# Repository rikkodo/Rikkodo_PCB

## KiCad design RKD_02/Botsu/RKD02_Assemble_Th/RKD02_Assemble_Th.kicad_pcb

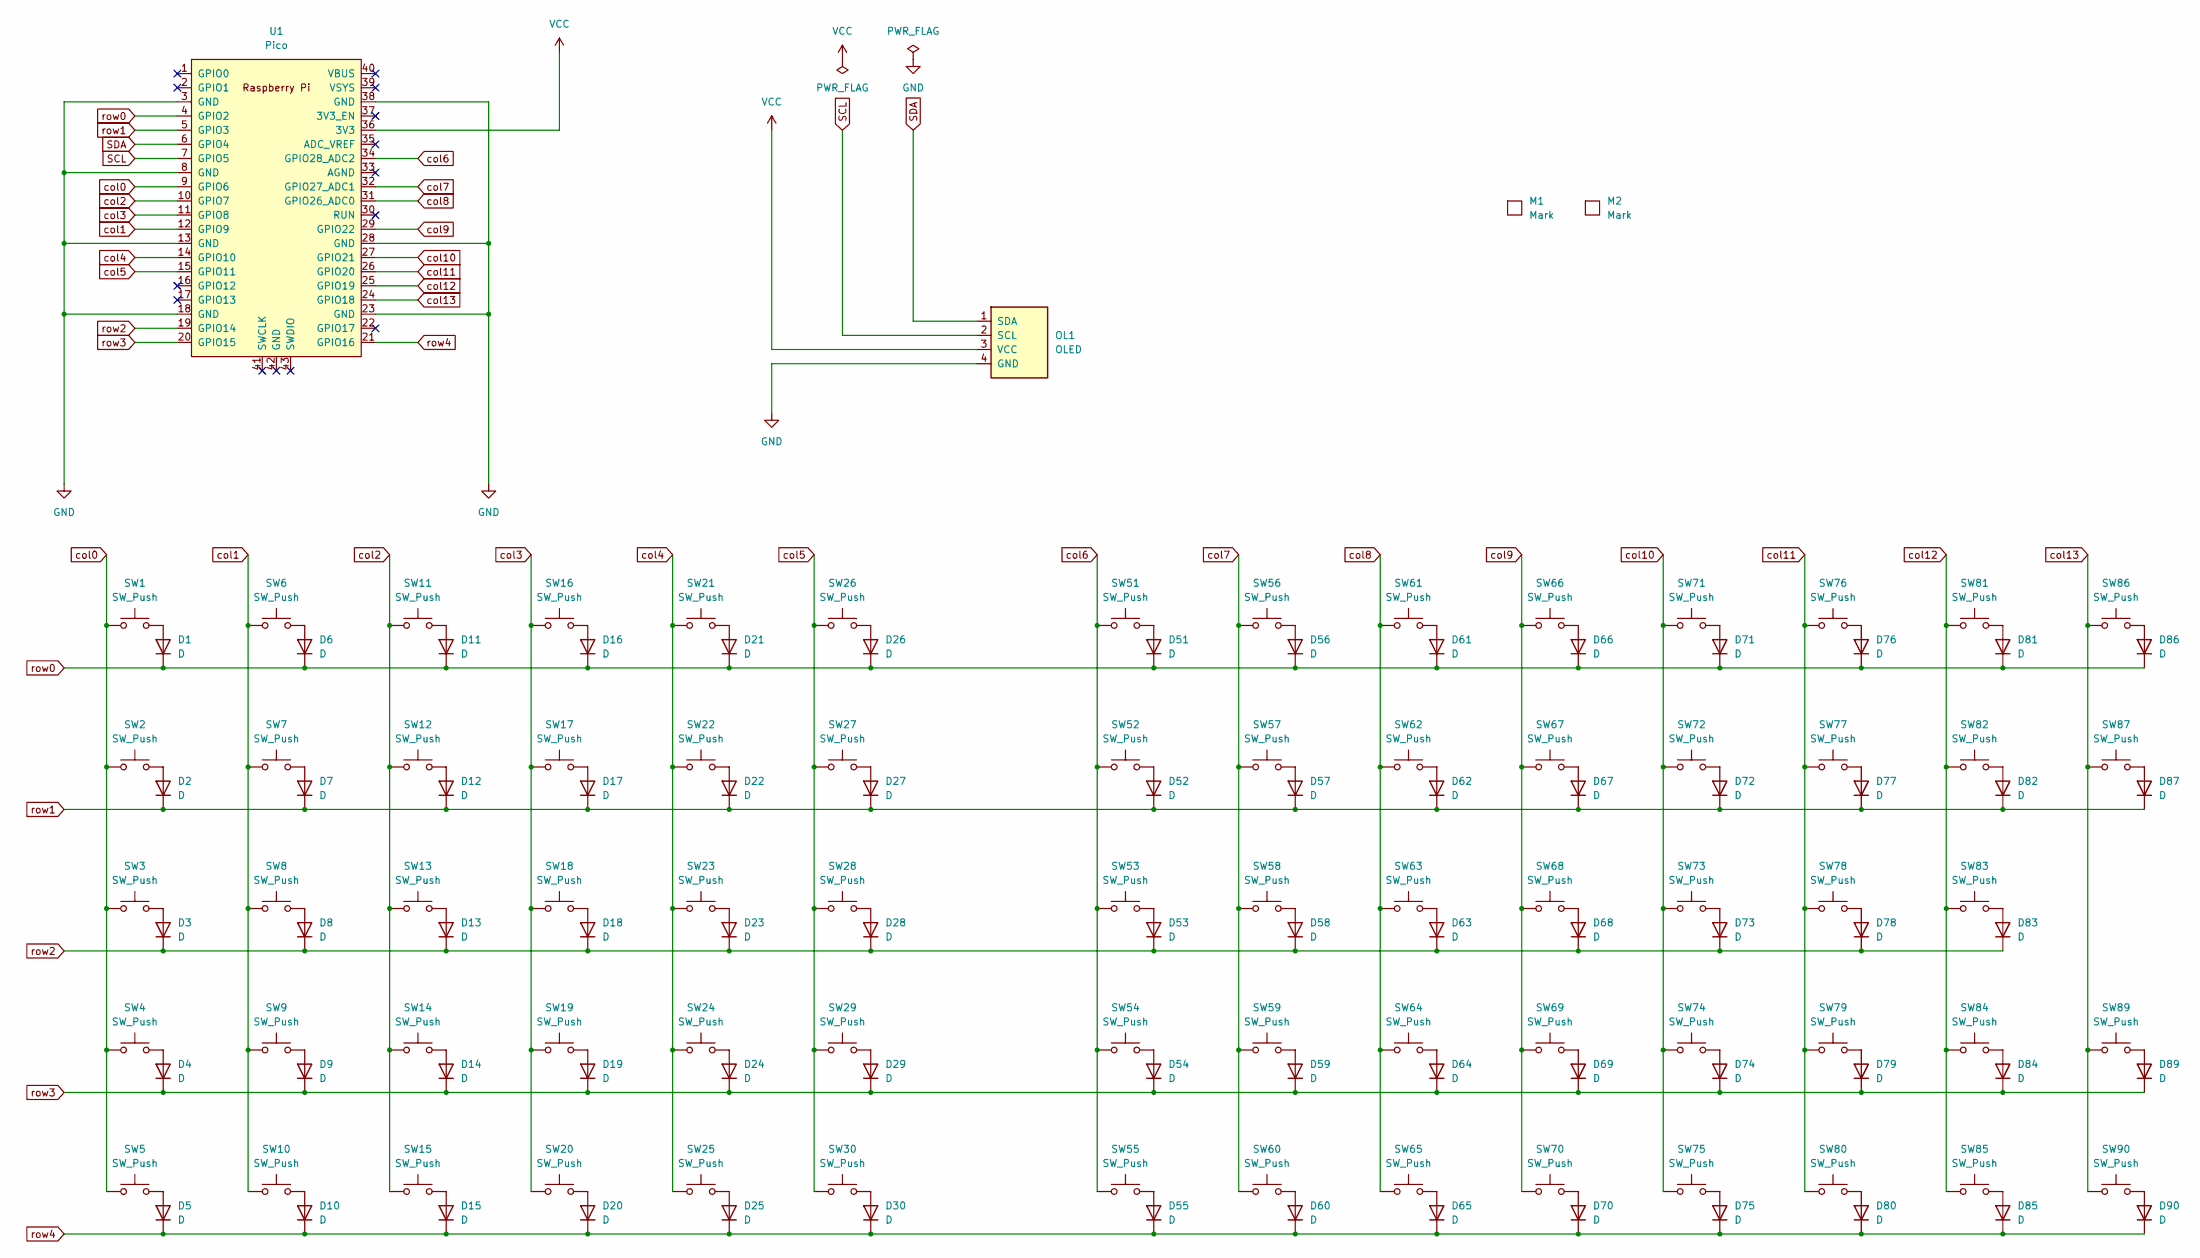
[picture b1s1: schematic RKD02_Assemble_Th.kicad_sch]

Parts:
D1, D2, D3, D4, D5, D6, D7, D8, D9, D10, D11, D12, D13, D14, D15, D16, D17, D18, D19, D20, D21, D22, D23, D24, D25, D26, D27, D28, D29, D30, D51, D52, D53, D54, D55, D56, D57, D58, D59, D60, D61, D62, D63, D64, D65, D66, D67, D68, D69, D70, D71, D72, D73, D74, D75, D76, D77, D78, D79, D80, D81, D82, D83, D84, D85, D86, D87, D89, D90: D; Diode_SMD
M1: Mark; rkd_Guard_Screw_Hall
M2: Mark; rkd_Point_Hall
OL1: OLED
SW1, SW2, SW3, SW5, SW6, SW7, SW8, SW9, SW10, SW11, SW12, SW13, SW14, SW15, SW16, SW17, SW18, SW19, SW20, SW21, SW22, SW23, SW24, SW26, SW27, SW28, SW29, SW30, SW51, SW52, SW53, SW54, SW55, SW56, SW57, SW58, SW59, SW60, SW61, SW62, SW63, SW64, SW65, SW66, SW67, SW68, SW69, SW70, SW71, SW72, SW73, SW74, SW75, SW76, SW77, SW78, SW79, SW80, SW81, SW82, SW84, SW85, SW87, SW89, SW90: SW_Push; rkd_Choc_v2_Hotswap_1u
SW4, SW25, SW83, SW86: SW_Push; rkd_Choc_v2_Hotswap_2u
U1: Pico; RPi_Pico_SMD_TH

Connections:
GND: OL1.4 (GND), U1.3 (GND), U1.8 (GND), U1.13 (GND), U1.18 (GND), U1.23 (GND), U1.28 (GND), U1.38 (GND)
unnamed: D1.2 (A), SW1.1
unnamed: D2.2 (A), SW2.1
unnamed: D3.2 (A), SW3.1
unnamed: D4.2 (A), SW4.1
unnamed: D5.2 (A), SW5.1
unnamed: D6.2 (A), SW6.1
unnamed: D7.2 (A), SW7.1
unnamed: D8.2 (A), SW8.1
unnamed: D9.2 (A), SW9.1
unnamed: D10.2 (A), SW10.1
unnamed: D11.2 (A), SW11.1
unnamed: D12.2 (A), SW12.1
unnamed: D13.2 (A), SW13.1
unnamed: D14.2 (A), SW14.1
unnamed: D15.2 (A), SW15.1
unnamed: D16.2 (A), SW16.1
unnamed: D17.2 (A), SW17.1
unnamed: D18.2 (A), SW18.1
unnamed: D19.2 (A), SW19.1
unnamed: D20.2 (A), SW20.1
unnamed: D21.2 (A), SW21.1
unnamed: D22.2 (A), SW22.1
unnamed: D23.2 (A), SW23.1
unnamed: D24.2 (A), SW24.1
unnamed: D25.2 (A), SW25.1
unnamed: D26.2 (A), SW26.1
unnamed: D27.2 (A), SW27.1
unnamed: D28.2 (A), SW28.1
unnamed: D29.2 (A), SW29.1
unnamed: D30.2 (A), SW30.1
unnamed: D51.2 (A), SW51.1
unnamed: D52.2 (A), SW52.1
unnamed: D53.2 (A), SW53.1
unnamed: D54.2 (A), SW54.1
unnamed: D55.2 (A), SW55.1
unnamed: D56.2 (A), SW56.1
unnamed: D57.2 (A), SW57.1
unnamed: D58.2 (A), SW58.1
unnamed: D59.2 (A), SW59.1
unnamed: D60.2 (A), SW60.1
unnamed: D61.2 (A), SW61.1
unnamed: D62.2 (A), SW62.1
unnamed: D63.2 (A), SW63.1
unnamed: D64.2 (A), SW64.1
unnamed: D65.2 (A), SW65.1
unnamed: D66.2 (A), SW66.1
unnamed: D67.2 (A), SW67.1
unnamed: D68.2 (A), SW68.1
unnamed: D69.2 (A), SW69.1
unnamed: D70.2 (A), SW70.1
unnamed: D71.2 (A), SW71.1
unnamed: D72.2 (A), SW72.1
unnamed: D73.2 (A), SW73.1
unnamed: D74.2 (A), SW74.1
unnamed: D75.2 (A), SW75.1
unnamed: D76.2 (A), SW76.1
unnamed: D77.2 (A), SW77.1
unnamed: D78.2 (A), SW78.1
unnamed: D79.2 (A), SW79.1
unnamed: D80.2 (A), SW80.1
unnamed: D81.2 (A), SW81.1
unnamed: D82.2 (A), SW82.1
unnamed: D83.2 (A), SW83.1
unnamed: D84.2 (A), SW84.1
unnamed: D85.2 (A), SW85.1
unnamed: D86.2 (A), SW86.1
unnamed: D87.2 (A), SW87.1
unnamed: D89.2 (A), SW89.1
unnamed: D90.2 (A), SW90.1
SCL: OL1.2 (SCL), U1.7 (GPIO5)
SDA: OL1.1 (SDA), U1.6 (GPIO4)
VCC: OL1.3 (VCC), U1.36 (3V3)
col0: SW1.2, SW2.2, SW3.2, SW4.2, SW5.2, U1.9 (GPIO6)
col1: SW6.2, SW7.2, SW8.2, SW9.2, SW10.2, U1.12 (GPIO9)
col2: SW11.2, SW12.2, SW13.2, SW14.2, SW15.2, U1.10 (GPIO7)
col3: SW16.2, SW17.2, SW18.2, SW19.2, SW20.2, U1.11 (GPIO8)
col4: SW21.2, SW22.2, SW23.2, SW24.2, SW25.2, U1.14 (GPIO10)
col5: SW26.2, SW27.2, SW28.2, SW29.2, SW30.2, U1.15 (GPIO11)
col6: SW51.2, SW52.2, SW53.2, SW54.2, SW55.2, U1.34 (GPIO28_ADC2)
col7: SW56.2, SW57.2, SW58.2, SW59.2, SW60.2, U1.32 (GPIO27_ADC1)
col8: SW61.2, SW62.2, SW63.2, SW64.2, SW65.2, U1.31 (GPIO26_ADC0)
col9: SW66.2, SW67.2, SW68.2, SW69.2, SW70.2, U1.29 (GPIO22)
col10: SW71.2, SW72.2, SW73.2, SW74.2, SW75.2, U1.27 (GPIO21)
col11: SW76.2, SW77.2, SW78.2, SW79.2, SW80.2, U1.26 (GPIO20)
col12: SW81.2, SW82.2, SW83.2, SW84.2, SW85.2, U1.25 (GPIO19)
col13: SW86.2, SW87.2, SW89.2, SW90.2, U1.24 (GPIO18)
row0: D1.1 (K), D6.1 (K), D11.1 (K), D16.1 (K), D21.1 (K), D26.1 (K), D51.1 (K), D56.1 (K), D61.1 (K), D66.1 (K), D71.1 (K), D76.1 (K), D81.1 (K), D86.1 (K), U1.4 (GPIO2)
row1: D2.1 (K), D7.1 (K), D12.1 (K), D17.1 (K), D22.1 (K), D27.1 (K), D52.1 (K), D57.1 (K), D62.1 (K), D67.1 (K), D72.1 (K), D77.1 (K), D82.1 (K), D87.1 (K), U1.5 (GPIO3)
row2: D3.1 (K), D8.1 (K), D13.1 (K), D18.1 (K), D23.1 (K), D28.1 (K), D53.1 (K), D58.1 (K), D63.1 (K), D68.1 (K), D73.1 (K), D78.1 (K), D83.1 (K), U1.19 (GPIO14)
row3: D4.1 (K), D9.1 (K), D14.1 (K), D19.1 (K), D24.1 (K), D29.1 (K), D54.1 (K), D59.1 (K), D64.1 (K), D69.1 (K), D74.1 (K), D79.1 (K), D84.1 (K), D89.1 (K), U1.20 (GPIO15)
row4: D5.1 (K), D10.1 (K), D15.1 (K), D20.1 (K), D25.1 (K), D30.1 (K), D55.1 (K), D60.1 (K), D65.1 (K), D70.1 (K), D75.1 (K), D80.1 (K), D85.1 (K), D90.1 (K), U1.21 (GPIO16)

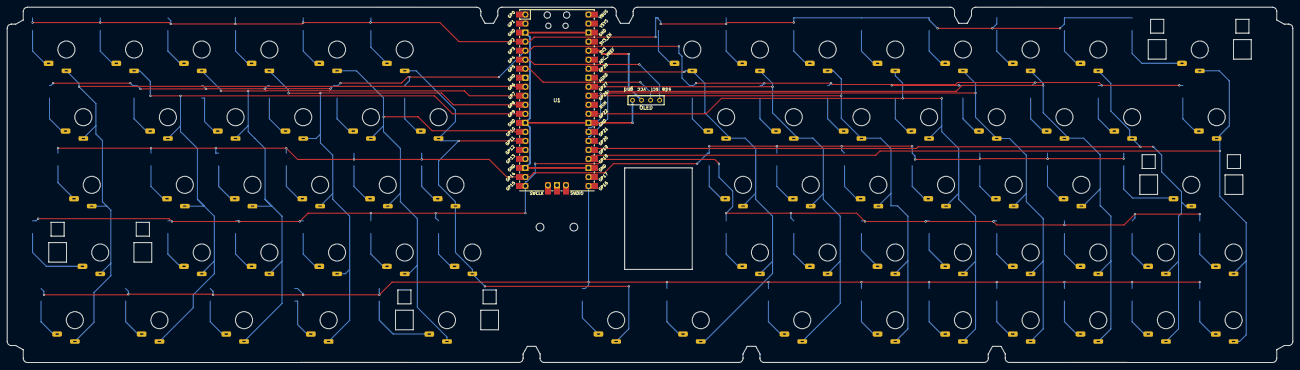
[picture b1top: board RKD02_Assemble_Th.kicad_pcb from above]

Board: 2 copper layers, 361.9 x 100.0 mm, 142 parts (0 on the bottom side), 92 nets.
